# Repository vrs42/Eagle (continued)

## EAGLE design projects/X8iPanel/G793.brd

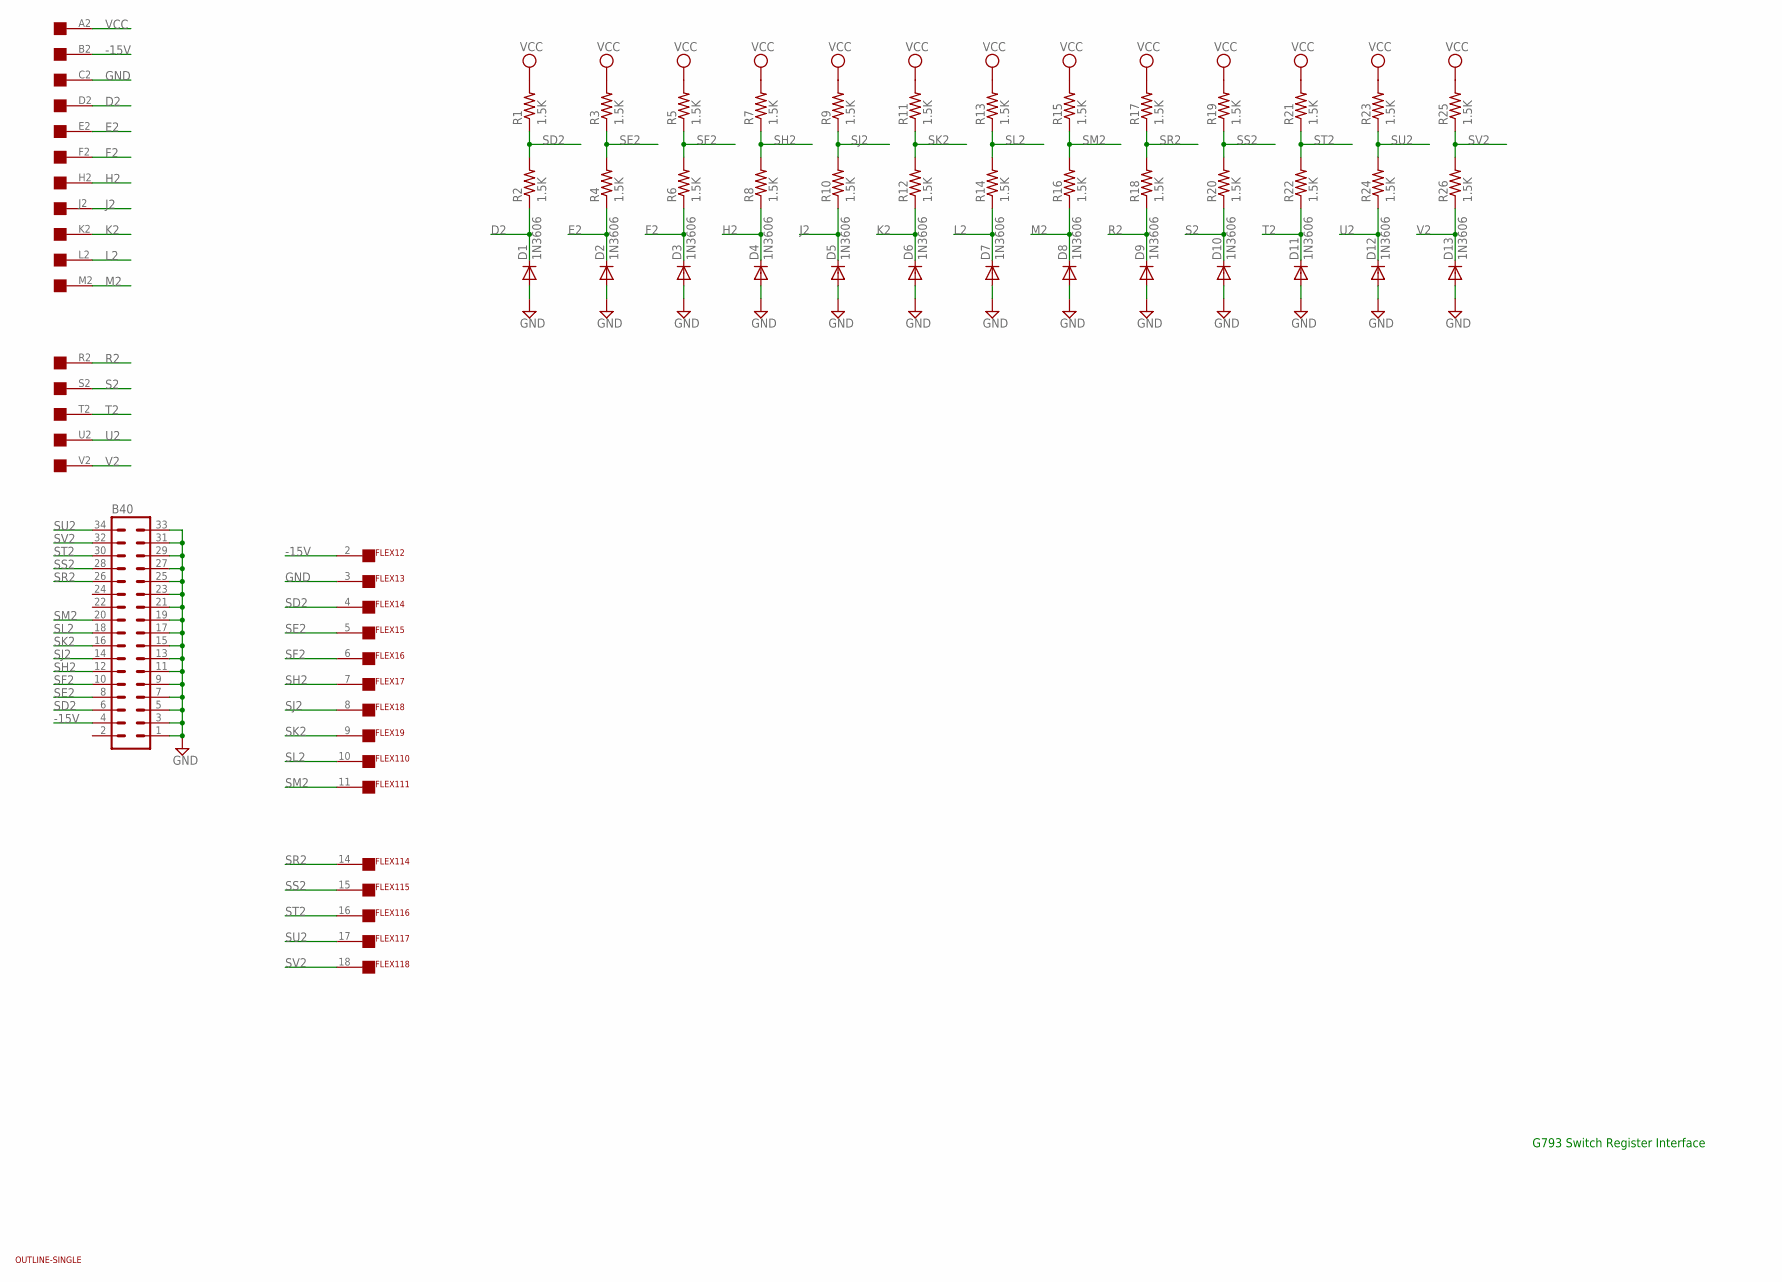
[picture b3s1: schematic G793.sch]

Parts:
B40: MA17-2
D1, D2, D3, D4, D5, D6, D7, D8, D9, D10, D11, D12, D13: 1N3606; DO35-10
FLEX1: FLEX19
R1, R2, R3, R4, R5, R6, R7, R8, R9, R10, R11, R12, R13, R14, R15, R16, R17, R18, R19, R20, R21, R22, R23, R24, R25, R26: 1.5K; 0207/10
U$1: OUTLINE-SINGLE; SINGLE
U$2: EDGE-1; EDGE-CON1

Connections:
-15V: B40.4, FLEX1.2, U$2.B2
D2: D1.C, R2.1, U$2.D2
E2: D2.C, R4.1, U$2.E2
F2: D3.C, R6.1, U$2.F2
GND: B40.1, B40.3, B40.5, B40.7, B40.9, B40.11, B40.13, B40.15, B40.17, B40.19, B40.21, B40.23, B40.25, B40.27, B40.29, B40.31, B40.33, D1.A, D2.A, D3.A, D4.A, D5.A, D6.A, D7.A, D8.A, D9.A, D10.A, D11.A, D12.A, D13.A, FLEX1.3, U$2.C2
H2: D4.C, R8.1, U$2.H2
J2: D5.C, R10.1, U$2.J2
K2: D6.C, R12.1, U$2.K2
L2: D7.C, R14.1, U$2.L2
M2: D8.C, R16.1, U$2.M2
R2: D9.C, R18.1, U$2.R2
S2: D10.C, R20.1, U$2.S2
SD2: B40.6, FLEX1.4, R1.1, R2.2
SE2: B40.8, FLEX1.5, R3.1, R4.2
SF2: B40.10, FLEX1.6, R5.1, R6.2
SH2: B40.12, FLEX1.7, R7.1, R8.2
SJ2: B40.14, FLEX1.8, R9.1, R10.2
SK2: B40.16, FLEX1.9, R11.1, R12.2
SL2: B40.18, FLEX1.10, R13.1, R14.2
SM2: B40.20, FLEX1.11, R15.1, R16.2
SR2: B40.26, FLEX1.14, R17.1, R18.2
SS2: B40.28, FLEX1.15, R19.1, R20.2
ST2: B40.30, FLEX1.16, R21.1, R22.2
SU2: B40.34, FLEX1.17, R23.1, R24.2
SV2: B40.32, FLEX1.18, R25.1, R26.2
T2: D11.C, R22.1, U$2.T2
U2: D12.C, R24.1, U$2.U2
V2: D13.C, R26.1, U$2.V2
VCC: R1.2, R3.2, R5.2, R7.2, R9.2, R11.2, R13.2, R15.2, R17.2, R19.2, R21.2, R23.2, R25.2, U$2.A2

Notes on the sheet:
G793 Switch Register Interface

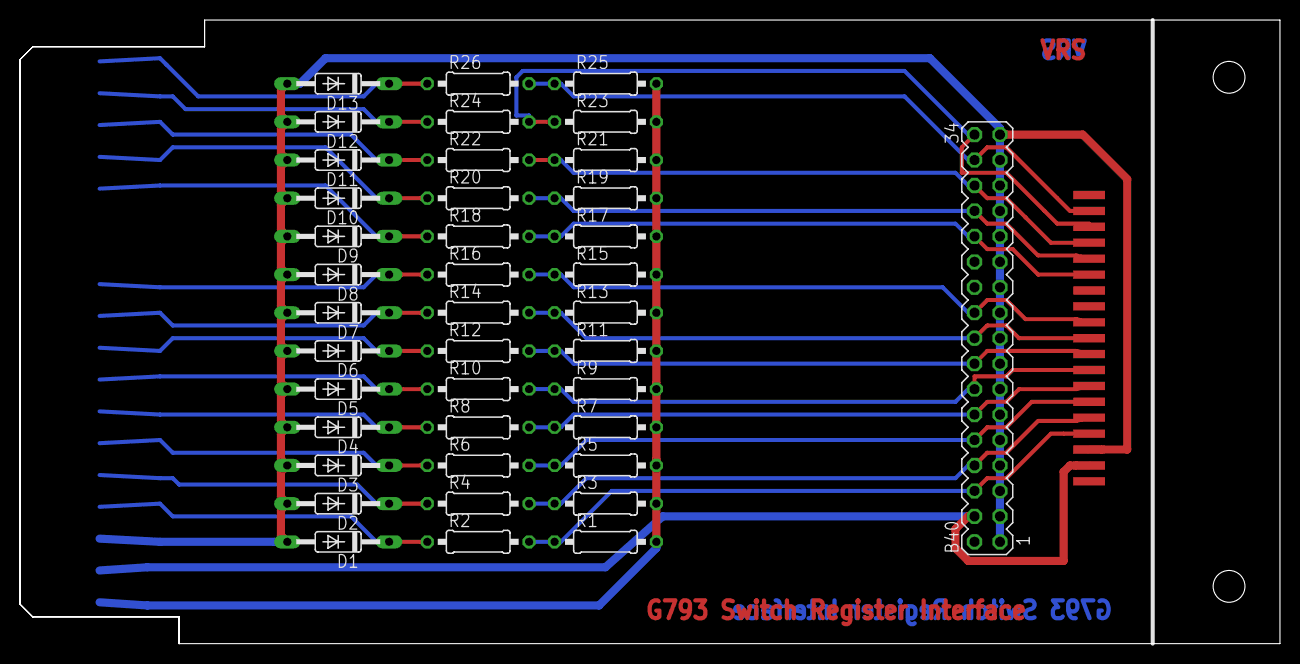
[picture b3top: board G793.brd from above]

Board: 2 copper layers, 125.7 x 62.2 mm, 43 parts (0 on the bottom side), 29 nets.

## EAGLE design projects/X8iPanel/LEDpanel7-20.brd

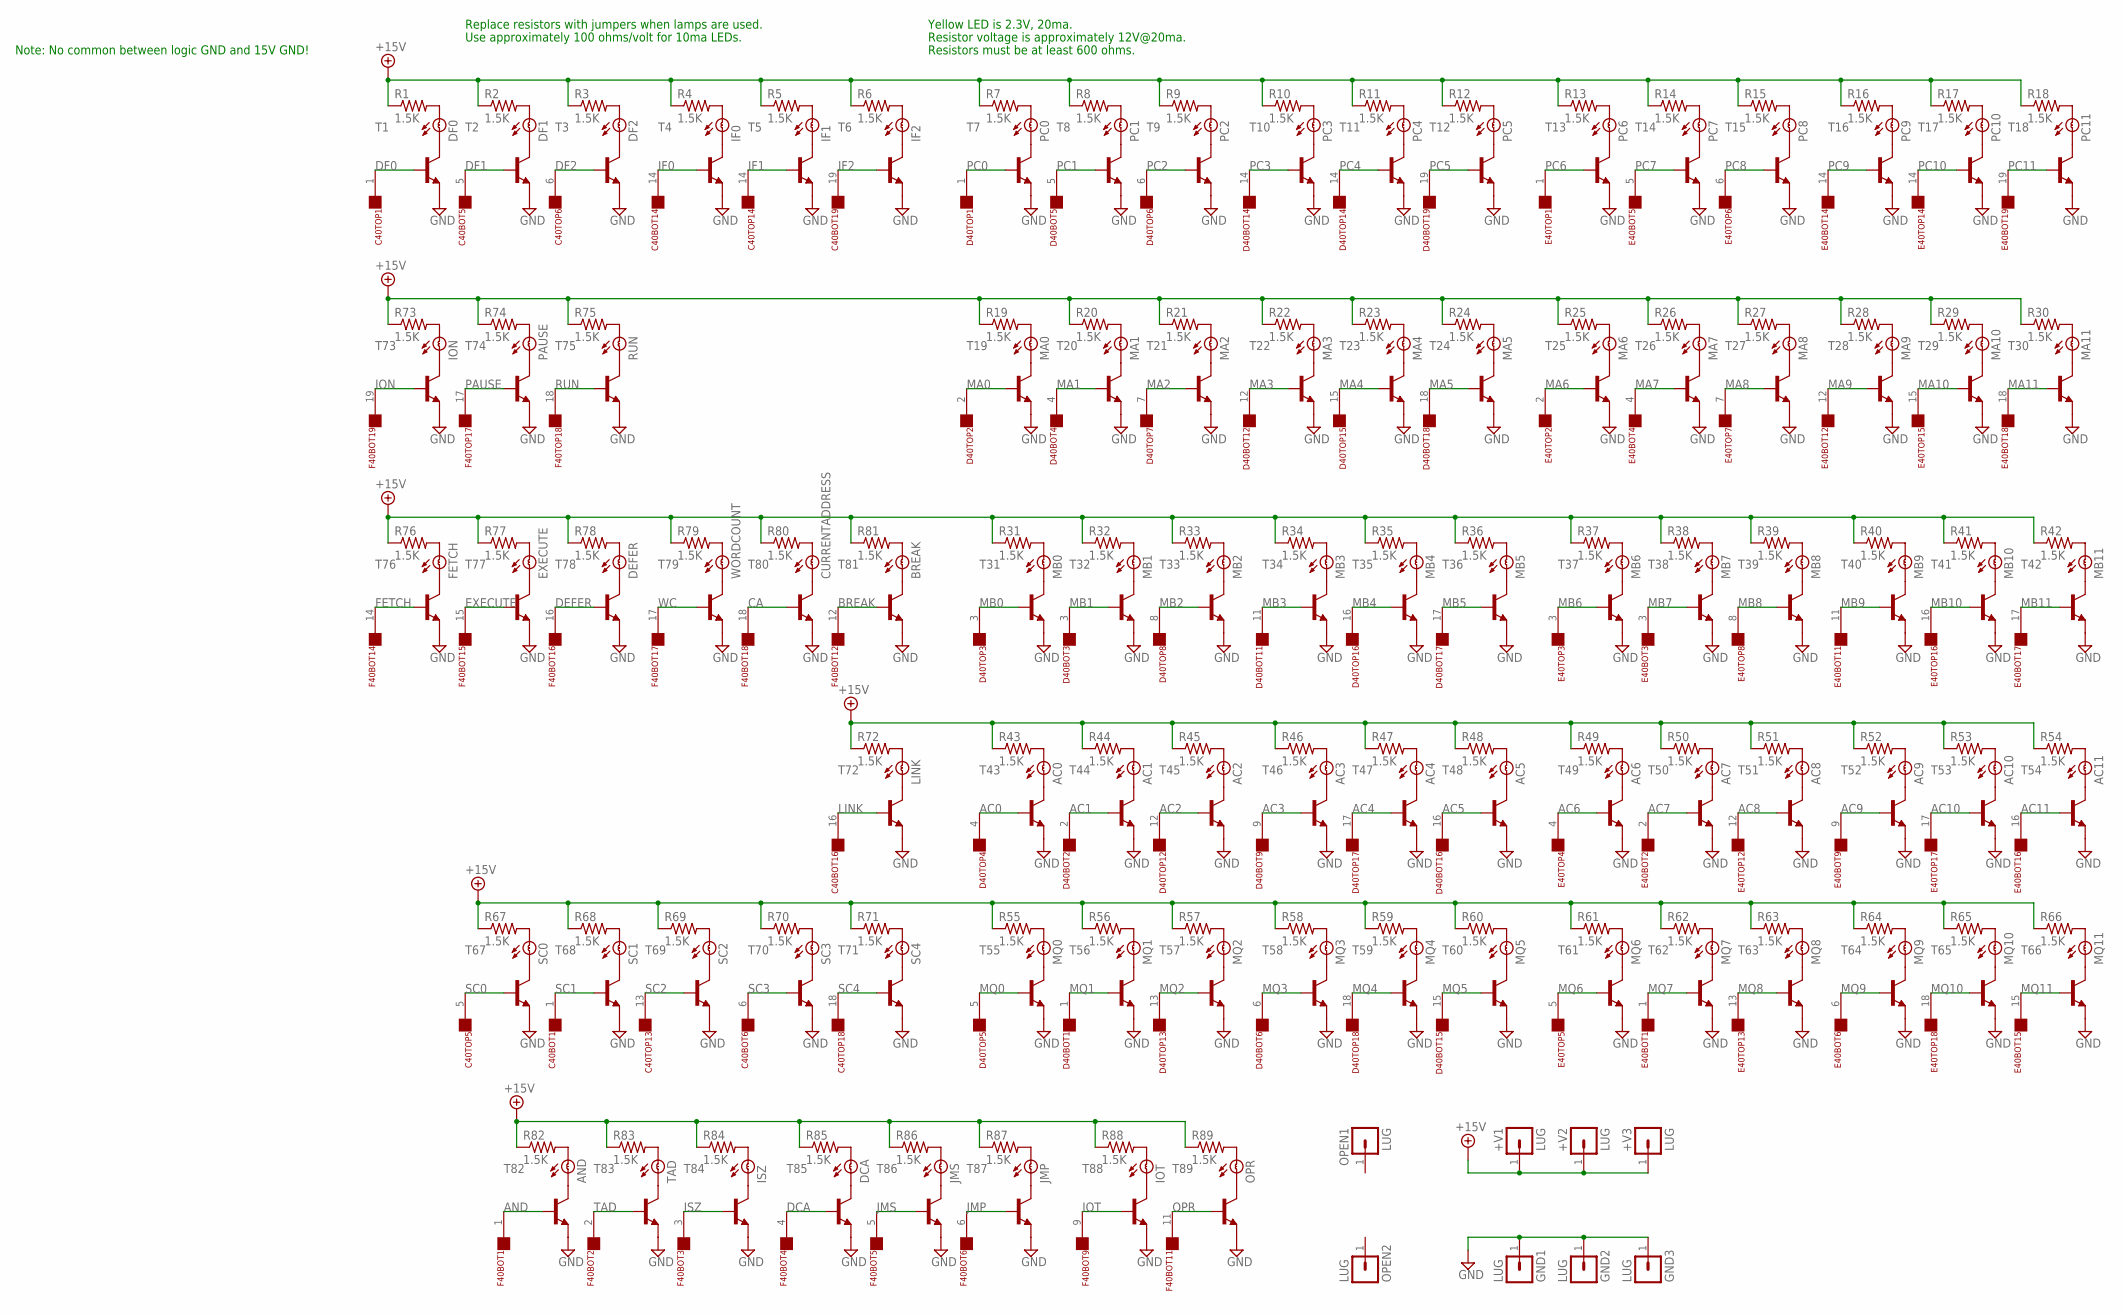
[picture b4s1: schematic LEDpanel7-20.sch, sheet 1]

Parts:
+V1, +V2, +V3: LUG; SPADELUG
AC0, AC1, AC2, AC3, AC4, AC5, AC6, AC7, AC8, AC9, AC10, AC11: BULB
AND: BULB
BREAK: BULB
C40BOT, C40TOP: FLEX19
CURRENTADDRESS: BULB
D40BOT, D40TOP: FLEX19
DCA: BULB
DEFER: BULB
DF0, DF1, DF2: BULB
E40BOT, E40TOP: FLEX19
EXECUTE: BULB
F40BOT, F40TOP: FLEX19
FETCH: BULB
GND1, GND2, GND3: LUG; SPADELUG
IF0, IF1, IF2: BULB
ION: BULB
IOT: BULB
ISZ: BULB
JMP: BULB
JMS: BULB
LINK: BULB
MA0, MA1, MA2, MA3, MA4, MA5, MA6, MA7, MA8, MA9, MA10, MA11: BULB
MB0, MB1, MB2, MB3, MB4, MB5, MB6, MB7, MB8, MB9, MB10, MB11: BULB
MQ0, MQ1, MQ2, MQ3, MQ4, MQ5, MQ6, MQ7, MQ8, MQ9, MQ10, MQ11: BULB
OPEN1, OPEN2: LUG; SPADELUG
OPR: BULB
PAUSE: BULB
PC0, PC1, PC2, PC3, PC4, PC5, PC6, PC7, PC8, PC9, PC10, PC11: BULB
R1, R2, R3, R4, R5, R6, R7, R8, R9, R10, R11, R12, R13, R14, R15, R16, R17, R18, R19, R20, R21, R22, R23, R24, R25, R26, R27, R28, R29, R30, R31, R32, R33, R34, R35, R36, R37, R38, R39, R40, R41, R42, R43, R44, R45, R46, R47, R48, R49, R50, R51, R52, R53, R54, R55, R56, R57, R58, R59, R60, R61, R62, R63, R64, R65, R66, R67, R68, R69, R70, R71, R72, R73, R74, R75, R76, R77, R78, R79, R80, R81, R82, R83, R84, R85, R86, R87, R88, R89: 1.5K; 0207/10
RUN: BULB
SC0, SC1, SC2, SC3, SC4: BULB
T1, T2, T3, T4, T5, T6, T7, T8, T9, T10, T11, T12, T13, T14, T15, T16, T17, T18, T19, T20, T21, T22, T23, T24, T25, T26, T27, T28, T29, T30, T31, T32, T33, T34, T35, T36, T37, T38, T39, T40, T41, T42, T43, T44, T45, T46, T47, T48, T49, T50, T51, T52, T53, T54, T55, T56, T57, T58, T59, T60, T61, T62, T63, T64, T65, T66, T67, T68, T69, T70, T71, T72, T73, T74, T75, T76, T77, T78, T79, T80, T81, T82, T83, T84, T85, T86, T87, T88, T89: MPS2222A-NPN-TO92-CBE; TO92-CBE
TAD: BULB
WORDCOUNT: BULB

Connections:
+15V: +V1.1, +V2.1, +V3.1, R1.1, R2.1, R3.1, R4.1, R5.1, R6.1, R7.1, R8.1, R9.1, R10.1, R11.1, R12.1, R13.1, R14.1, R15.1, R16.1, R17.1, R18.1, R19.1, R20.1, R21.1, R22.1, R23.1, R24.1, R25.1, R26.1, R27.1, R28.1, R29.1, R30.1, R31.1, R32.1, R33.1, R34.1, R35.1, R36.1, R37.1, R38.1, R39.1, R40.1, R41.1, R42.1, R43.1, R44.1, R45.1, R46.1, R47.1, R48.1, R49.1, R50.1, R51.1, R52.1, R53.1, R54.1, R55.1, R56.1, R57.1, R58.1, R59.1, R60.1, R61.1, R62.1, R63.1, R64.1, R65.1, R66.1, R67.1, R68.1, R69.1, R70.1, R71.1, R72.1, R73.1, R74.1, R75.1, R76.1, R77.1, R78.1, R79.1, R80.1, R81.1, R82.1, R83.1, R84.1, R85.1, R86.1, R87.1, R88.1, R89.1
AC0: D40TOP.4, T43.B; also elsewhere on the board
AC1: D40BOT.2, T44.B; also elsewhere on the board
AC2: D40TOP.12, T45.B; also elsewhere on the board
AC3: D40BOT.9, T46.B; also elsewhere on the board
AC4: D40TOP.17, T47.B; also elsewhere on the board
AC5: D40BOT.16, T48.B; also elsewhere on the board
AC6: E40TOP.4, T49.B; also elsewhere on the board
AC7: E40BOT.2, T50.B; also elsewhere on the board
AC8: E40TOP.12, T51.B; also elsewhere on the board
AC9: E40BOT.9, T52.B; also elsewhere on the board
AC10: E40TOP.17, T53.B; also elsewhere on the board
AC11: E40BOT.16, T54.B; also elsewhere on the board
AND: F40BOT.1, T82.B; also elsewhere on the board
BREAK: F40BOT.12, T81.B; also elsewhere on the board
CA: F40BOT.18, T80.B; also elsewhere on the board
DCA: F40BOT.4, T85.B; also elsewhere on the board
DEFER: F40BOT.16, T78.B; also elsewhere on the board
DF0: C40TOP.1, T1.B; also elsewhere on the board
DF1: C40BOT.5, T2.B; also elsewhere on the board
DF2: C40TOP.6, T3.B; also elsewhere on the board
EXECUTE: F40BOT.15, T77.B; also elsewhere on the board
FETCH: F40BOT.14, T76.B; also elsewhere on the board
GND: GND1.1, GND2.1, GND3.1, T1.E, T2.E, T3.E, T4.E, T5.E, T6.E, T7.E, T8.E, T9.E, T10.E, T11.E, T12.E, T13.E, T14.E, T15.E, T16.E, T17.E, T18.E, T19.E, T20.E, T21.E, T22.E, T23.E, T24.E, T25.E, T26.E, T27.E, T28.E, T29.E, T30.E, T31.E, T32.E, T33.E, T34.E, T35.E, T36.E, T37.E, T38.E, T39.E, T40.E, T41.E, T42.E, T43.E, T44.E, T45.E, T46.E, T47.E, T48.E, T49.E, T50.E, T51.E, T52.E, T53.E, T54.E, T55.E, T56.E, T57.E, T58.E, T59.E, T60.E, T61.E, T62.E, T63.E, T64.E, T65.E, T66.E, T67.E, T68.E, T69.E, T70.E, T71.E, T72.E, T73.E, T74.E, T75.E, T76.E, T77.E, T78.E, T79.E, T80.E, T81.E, T82.E, T83.E, T84.E, T85.E, T86.E, T87.E, T88.E, T89.E
IF0: C40BOT.14, T4.B; also elsewhere on the board
IF1: C40TOP.14, T5.B; also elsewhere on the board
IF2: C40BOT.19, T6.B; also elsewhere on the board
ION: F40BOT.19, T73.B; also elsewhere on the board
IOT: F40BOT.9, T88.B; also elsewhere on the board
ISZ: F40BOT.3, T84.B; also elsewhere on the board
JMP: F40BOT.6, T87.B; also elsewhere on the board
JMS: F40BOT.5, T86.B; also elsewhere on the board
LINK: C40BOT.16, T72.B; also elsewhere on the board
MA0: D40TOP.2, T19.B; also elsewhere on the board
MA1: D40BOT.4, T20.B; also elsewhere on the board
MA2: D40TOP.7, T21.B; also elsewhere on the board
MA3: D40BOT.12, T22.B; also elsewhere on the board
MA4: D40TOP.15, T23.B; also elsewhere on the board
MA5: D40BOT.18, T24.B; also elsewhere on the board
MA6: E40TOP.2, T25.B; also elsewhere on the board
MA7: E40BOT.4, T26.B; also elsewhere on the board
MA8: E40TOP.7, T27.B; also elsewhere on the board
MA9: E40BOT.12, T28.B; also elsewhere on the board
MA10: E40TOP.15, T29.B; also elsewhere on the board
MA11: E40BOT.18, T30.B; also elsewhere on the board
MB0: D40TOP.3, T31.B; also elsewhere on the board
MB1: D40BOT.3, T32.B; also elsewhere on the board
MB2: D40TOP.8, T33.B; also elsewhere on the board
MB3: D40BOT.11, T34.B; also elsewhere on the board
MB4: D40TOP.16, T35.B; also elsewhere on the board
MB5: D40BOT.17, T36.B; also elsewhere on the board
MB6: E40TOP.3, T37.B; also elsewhere on the board
MB7: E40BOT.3, T38.B; also elsewhere on the board
MB8: E40TOP.8, T39.B; also elsewhere on the board
MB9: E40BOT.11, T40.B; also elsewhere on the board
MB10: E40TOP.16, T41.B; also elsewhere on the board
MB11: E40BOT.17, T42.B; also elsewhere on the board
MQ0: D40TOP.5, T55.B; also elsewhere on the board
MQ1: D40BOT.1, T56.B; also elsewhere on the board
MQ2: D40TOP.13, T57.B; also elsewhere on the board
MQ3: D40BOT.6, T58.B; also elsewhere on the board
MQ4: D40TOP.18, T59.B; also elsewhere on the board
MQ5: D40BOT.15, T60.B; also elsewhere on the board
MQ6: E40TOP.5, T61.B; also elsewhere on the board
MQ7: E40BOT.1, T62.B; also elsewhere on the board
MQ8: E40TOP.13, T63.B; also elsewhere on the board
MQ9: E40BOT.6, T64.B; also elsewhere on the board
MQ10: E40TOP.18, T65.B; also elsewhere on the board
MQ11: E40BOT.15, T66.B; also elsewhere on the board
unnamed: DF0.B, T1.C
unnamed: DF1.B, T2.C
unnamed: DF2.B, T3.C
unnamed: IF0.B, T4.C
unnamed: IF1.B, T5.C
unnamed: IF2.B, T6.C
unnamed: PC0.B, T7.C
unnamed: PC1.B, T8.C
unnamed: PC2.B, T9.C
unnamed: PC3.B, T10.C
unnamed: PC4.B, T11.C
unnamed: PC5.B, T12.C
unnamed: PC6.B, T13.C
unnamed: PC7.B, T14.C
unnamed: PC8.B, T15.C
unnamed: PC9.B, T16.C
unnamed: PC10.B, T17.C
unnamed: PC11.B, T18.C
unnamed: MA0.B, T19.C
unnamed: MA1.B, T20.C
unnamed: MA2.B, T21.C
unnamed: MA3.B, T22.C
unnamed: MA4.B, T23.C
unnamed: MA5.B, T24.C
unnamed: MA6.B, T25.C
unnamed: MA7.B, T26.C
unnamed: MA8.B, T27.C
unnamed: MA9.B, T28.C
unnamed: MA10.B, T29.C
unnamed: MA11.B, T30.C
unnamed: MB0.B, T31.C
unnamed: MB1.B, T32.C
unnamed: MB2.B, T33.C
unnamed: MB3.B, T34.C
unnamed: MB4.B, T35.C
unnamed: MB5.B, T36.C
unnamed: MB6.B, T37.C
unnamed: MB7.B, T38.C
unnamed: MB8.B, T39.C
unnamed: MB9.B, T40.C
unnamed: MB10.B, T41.C
unnamed: MB11.B, T42.C
unnamed: AC0.B, T43.C
unnamed: AC1.B, T44.C
unnamed: AC2.B, T45.C
unnamed: AC3.B, T46.C
unnamed: AC4.B, T47.C
unnamed: AC5.B, T48.C
unnamed: AC6.B, T49.C
unnamed: AC7.B, T50.C
unnamed: AC8.B, T51.C
unnamed: AC9.B, T52.C
unnamed: AC10.B, T53.C
unnamed: AC11.B, T54.C
unnamed: MQ0.B, T55.C
unnamed: MQ1.B, T56.C
unnamed: MQ2.B, T57.C
unnamed: MQ3.B, T58.C
unnamed: MQ4.B, T59.C
unnamed: MQ5.B, T60.C
unnamed: MQ6.B, T61.C
unnamed: MQ7.B, T62.C
unnamed: MQ8.B, T63.C
unnamed: MQ9.B, T64.C
unnamed: MQ10.B, T65.C
unnamed: MQ11.B, T66.C
unnamed: SC0.B, T67.C
unnamed: SC1.B, T68.C
unnamed: SC2.B, T69.C
unnamed: SC3.B, T70.C
unnamed: SC4.B, T71.C
unnamed: LINK.B, T72.C
unnamed: ION.B, T73.C
unnamed: PAUSE.B, T74.C
unnamed: RUN.B, T75.C
unnamed: FETCH.B, T76.C
unnamed: EXECUTE.B, T77.C
unnamed: DEFER.B, T78.C
unnamed: T79.C, WORDCOUNT.B
unnamed: CURRENTADDRESS.B, T80.C
unnamed: BREAK.B, T81.C
unnamed: AND.B, T82.C
unnamed: T83.C, TAD.B
unnamed: ISZ.B, T84.C
unnamed: DCA.B, T85.C
unnamed: JMS.B, T86.C
unnamed: JMP.B, T87.C
unnamed: IOT.B, T88.C
unnamed: OPR.B, T89.C
unnamed: DF0.A, R1.2
unnamed: DF1.A, R2.2
unnamed: DF2.A, R3.2
unnamed: IF0.A, R4.2
unnamed: IF1.A, R5.2
unnamed: IF2.A, R6.2
unnamed: PC0.A, R7.2
unnamed: PC1.A, R8.2
unnamed: PC2.A, R9.2
unnamed: PC3.A, R10.2
unnamed: PC4.A, R11.2
unnamed: PC5.A, R12.2
unnamed: PC6.A, R13.2
unnamed: PC7.A, R14.2
unnamed: PC8.A, R15.2
unnamed: PC9.A, R16.2
unnamed: PC10.A, R17.2
unnamed: PC11.A, R18.2
unnamed: ION.A, R73.2
unnamed: PAUSE.A, R74.2
unnamed: R75.2, RUN.A
unnamed: MA0.A, R19.2
unnamed: MA1.A, R20.2
unnamed: MA2.A, R21.2
unnamed: MA3.A, R22.2
unnamed: MA4.A, R23.2
unnamed: MA5.A, R24.2
unnamed: MA6.A, R25.2
unnamed: MA7.A, R26.2
unnamed: MA8.A, R27.2
unnamed: MA9.A, R28.2
unnamed: MA10.A, R29.2
unnamed: MA11.A, R30.2
unnamed: FETCH.A, R76.2
unnamed: EXECUTE.A, R77.2
unnamed: DEFER.A, R78.2
unnamed: R79.2, WORDCOUNT.A
unnamed: CURRENTADDRESS.A, R80.2
unnamed: BREAK.A, R81.2
unnamed: LINK.A, R72.2
unnamed: MB0.A, R31.2
unnamed: MB1.A, R32.2
unnamed: MB2.A, R33.2
unnamed: MB3.A, R34.2
unnamed: MB4.A, R35.2
unnamed: MB5.A, R36.2
unnamed: MB6.A, R37.2
unnamed: MB7.A, R38.2
unnamed: MB8.A, R39.2
unnamed: MB9.A, R40.2
unnamed: MB10.A, R41.2
unnamed: MB11.A, R42.2
unnamed: AC0.A, R43.2
unnamed: AC1.A, R44.2
unnamed: AC2.A, R45.2
unnamed: AC3.A, R46.2
unnamed: AC4.A, R47.2
unnamed: AC5.A, R48.2
unnamed: AC6.A, R49.2
unnamed: AC7.A, R50.2
unnamed: AC8.A, R51.2
unnamed: AC9.A, R52.2
unnamed: AC10.A, R53.2
unnamed: AC11.A, R54.2
unnamed: R67.2, SC0.A
unnamed: R68.2, SC1.A
unnamed: R69.2, SC2.A
unnamed: R70.2, SC3.A
unnamed: R71.2, SC4.A
unnamed: MQ11.A, R66.2
unnamed: MQ10.A, R65.2
unnamed: MQ9.A, R64.2
unnamed: MQ8.A, R63.2
unnamed: MQ7.A, R62.2
unnamed: MQ6.A, R61.2
unnamed: MQ5.A, R60.2
unnamed: MQ4.A, R59.2
unnamed: MQ3.A, R58.2
unnamed: MQ2.A, R57.2
unnamed: MQ1.A, R56.2
unnamed: MQ0.A, R55.2
unnamed: AND.A, R82.2
unnamed: R83.2, TAD.A
unnamed: ISZ.A, R84.2
unnamed: DCA.A, R85.2
unnamed: JMS.A, R86.2
unnamed: JMP.A, R87.2
unnamed: IOT.A, R88.2
unnamed: OPR.A, R89.2
OPR: F40BOT.11, T89.B; also elsewhere on the board
PAUSE: F40TOP.17, T74.B; also elsewhere on the board
PC0: D40TOP.1, T7.B; also elsewhere on the board
PC1: D40BOT.5, T8.B; also elsewhere on the board
PC2: D40TOP.6, T9.B; also elsewhere on the board
PC3: D40BOT.14, T10.B; also elsewhere on the board
PC4: D40TOP.14, T11.B; also elsewhere on the board
PC5: D40BOT.19, T12.B; also elsewhere on the board
PC6: E40TOP.1, T13.B; also elsewhere on the board
PC7: E40BOT.5, T14.B; also elsewhere on the board
PC8: E40TOP.6, T15.B; also elsewhere on the board
PC9: E40BOT.14, T16.B; also elsewhere on the board
PC10: E40TOP.14, T17.B; also elsewhere on the board
PC11: E40BOT.19, T18.B; also elsewhere on the board
RUN: F40TOP.18, T75.B; also elsewhere on the board
SC0: C40TOP.5, T67.B; also elsewhere on the board
SC1: C40BOT.1, T68.B; also elsewhere on the board
SC2: C40TOP.13, T69.B; also elsewhere on the board
SC3: C40BOT.6, T70.B; also elsewhere on the board
SC4: C40TOP.18, T71.B; also elsewhere on the board
TAD: F40BOT.2, T83.B; also elsewhere on the board
WC: F40BOT.17, T79.B; also elsewhere on the board

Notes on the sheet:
Replace resistors with jumpers when lamps are used.
Use approximately 100 ohms/volt for 10ma LEDs.
Yellow LED is 2.3V, 20ma.
Resistor voltage is approximately 12V@20ma.
Resistors must be at least 600 ohms.
Note: No common between logic GND and 15V GND!

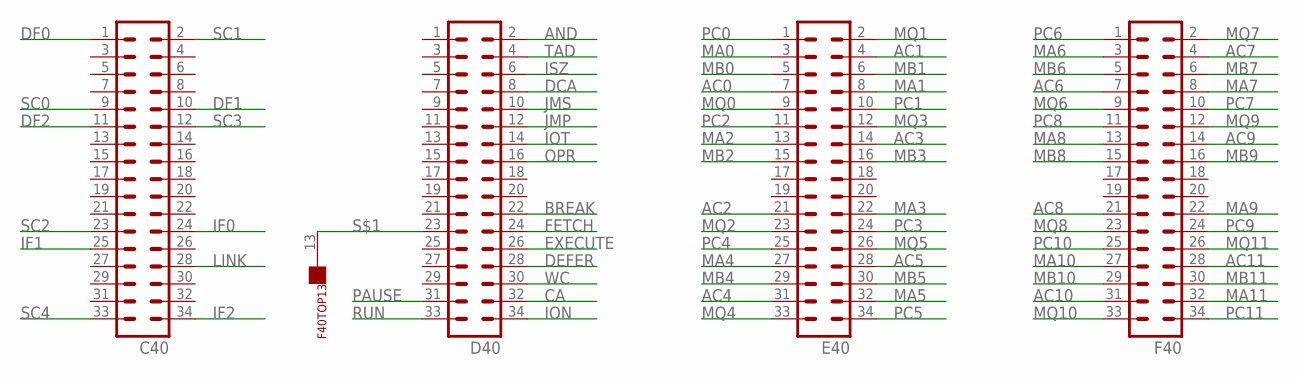
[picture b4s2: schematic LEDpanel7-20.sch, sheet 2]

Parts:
C40: ML34
D40: ML34
E40: ML34
F40: ML34
F40TOP: FLEX19

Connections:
AC0: E40.7; also elsewhere on the board
AC1: E40.4; also elsewhere on the board
AC2: E40.21; also elsewhere on the board
AC3: E40.14; also elsewhere on the board
AC4: E40.31; also elsewhere on the board
AC5: E40.28; also elsewhere on the board
AC6: F40.7; also elsewhere on the board
AC7: F40.4; also elsewhere on the board
AC8: F40.21; also elsewhere on the board
AC9: F40.14; also elsewhere on the board
AC10: F40.31; also elsewhere on the board
AC11: F40.28; also elsewhere on the board
AND: D40.2; also elsewhere on the board
BREAK: D40.22; also elsewhere on the board
CA: D40.32; also elsewhere on the board
DCA: D40.8; also elsewhere on the board
DEFER: D40.28; also elsewhere on the board
DF0: C40.1; also elsewhere on the board
DF1: C40.10; also elsewhere on the board
DF2: C40.11; also elsewhere on the board
EXECUTE: D40.26; also elsewhere on the board
FETCH: D40.24; also elsewhere on the board
IF0: C40.24; also elsewhere on the board
IF1: C40.25; also elsewhere on the board
IF2: C40.34; also elsewhere on the board
ION: D40.34; also elsewhere on the board
IOT: D40.14; also elsewhere on the board
ISZ: D40.6; also elsewhere on the board
JMP: D40.12; also elsewhere on the board
JMS: D40.10; also elsewhere on the board
LINK: C40.28; also elsewhere on the board
MA0: E40.3; also elsewhere on the board
MA1: E40.8; also elsewhere on the board
MA2: E40.13; also elsewhere on the board
MA3: E40.22; also elsewhere on the board
MA4: E40.27; also elsewhere on the board
MA5: E40.32; also elsewhere on the board
MA6: F40.3; also elsewhere on the board
MA7: F40.8; also elsewhere on the board
MA8: F40.13; also elsewhere on the board
MA9: F40.22; also elsewhere on the board
MA10: F40.27; also elsewhere on the board
MA11: F40.32; also elsewhere on the board
MB0: E40.5; also elsewhere on the board
MB1: E40.6; also elsewhere on the board
MB2: E40.15; also elsewhere on the board
MB3: E40.16; also elsewhere on the board
MB4: E40.29; also elsewhere on the board
MB5: E40.30; also elsewhere on the board
MB6: F40.5; also elsewhere on the board
MB7: F40.6; also elsewhere on the board
MB8: F40.15; also elsewhere on the board
MB9: F40.16; also elsewhere on the board
MB10: F40.29; also elsewhere on the board
MB11: F40.30; also elsewhere on the board
MQ0: E40.9; also elsewhere on the board
MQ1: E40.2; also elsewhere on the board
MQ2: E40.23; also elsewhere on the board
MQ3: E40.12; also elsewhere on the board
MQ4: E40.33; also elsewhere on the board
MQ5: E40.26; also elsewhere on the board
MQ6: F40.9; also elsewhere on the board
MQ7: F40.2; also elsewhere on the board
MQ8: F40.23; also elsewhere on the board
MQ9: F40.12; also elsewhere on the board
MQ10: F40.33; also elsewhere on the board
MQ11: F40.26; also elsewhere on the board
OPR: D40.16; also elsewhere on the board
PAUSE: D40.31; also elsewhere on the board
PC0: E40.1; also elsewhere on the board
PC1: E40.10; also elsewhere on the board
PC2: E40.11; also elsewhere on the board
PC3: E40.24; also elsewhere on the board
PC4: E40.25; also elsewhere on the board
PC5: E40.34; also elsewhere on the board
PC6: F40.1; also elsewhere on the board
PC7: F40.10; also elsewhere on the board
PC8: F40.11; also elsewhere on the board
PC9: F40.24; also elsewhere on the board
PC10: F40.25; also elsewhere on the board
PC11: F40.34; also elsewhere on the board
RUN: D40.33; also elsewhere on the board
S$1: D40.23, F40TOP.13
SC0: C40.9; also elsewhere on the board
SC1: C40.2; also elsewhere on the board
SC2: C40.23; also elsewhere on the board
SC3: C40.12; also elsewhere on the board
SC4: C40.33; also elsewhere on the board
TAD: D40.4; also elsewhere on the board
WC: D40.30; also elsewhere on the board

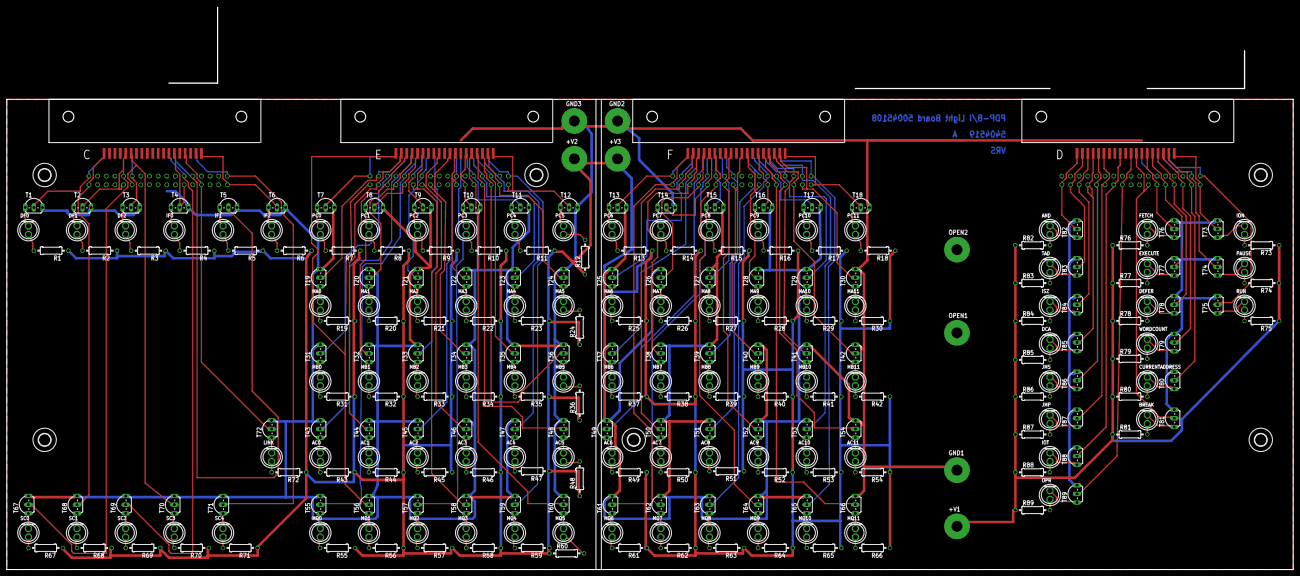
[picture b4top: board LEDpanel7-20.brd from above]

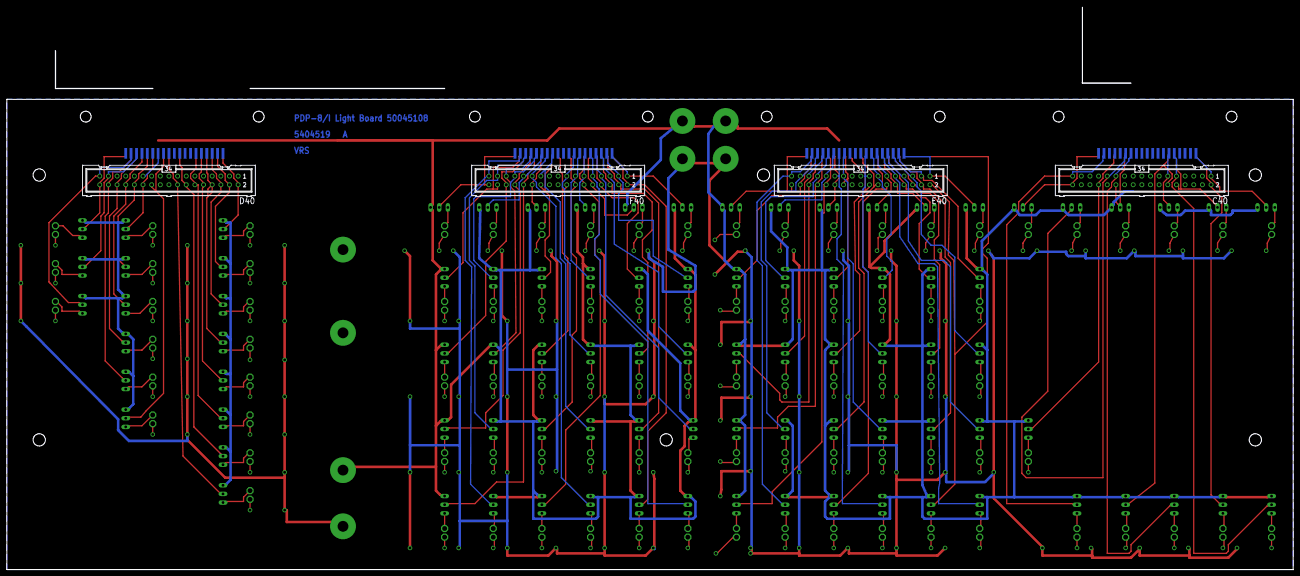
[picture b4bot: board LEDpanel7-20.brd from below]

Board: 2 copper layers, 377.8 x 138.1 mm, 297 parts (8 on the bottom side), 270 nets.

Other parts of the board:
U$1, U$2, U$3, U$4: STRAIN-RELIEF
U$5, U$6, U$7, U$8, U$9, U$11: 3,6
